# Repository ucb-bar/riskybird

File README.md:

# RiskyBird

RiskyBird is an experimental quadcopter platform for hardware-software-mechanical co-design of tiny autonomous robots.

## Overview

This repository contains multiple iterations of RiskyBird hardware designs:

- **riskybirdv2_sensor/** - Sensor board with IMU, optical flow, and camera interface
- **riskybirdv2_esp/** - ESP32-based flight controller
- **riskybirdv2_k230d/** - K230D-based compute module
- **riskybirdv3_base/** - Latest iteration with integrated base board design
- **ecad/** & **ecad_2025/** - Electronic CAD files and libraries

## Design Goals

- Miniaturized form factor for agile flight
- Modular sensor and compute architecture
- On-board ML inference capability
- Rapid prototyping and iteration

## Hardware

The platform uses KiCad for PCB design and integrates:
- Low-cost sensors (IMU, optical flow, cameras)
- ESP32 for real-time control
- Optional AI accelerator (K230D) for perception
- Custom power distribution and motor control

## Educational Content

See [riskybird-academy/](riskybird-academy/) for tutorial materials covering embedded ML, robotics, and reinforcement learning.

## License

Hardware designs and educational materials are open source for non-commercial use.

Contact: vnikiforov@berkeley.edu

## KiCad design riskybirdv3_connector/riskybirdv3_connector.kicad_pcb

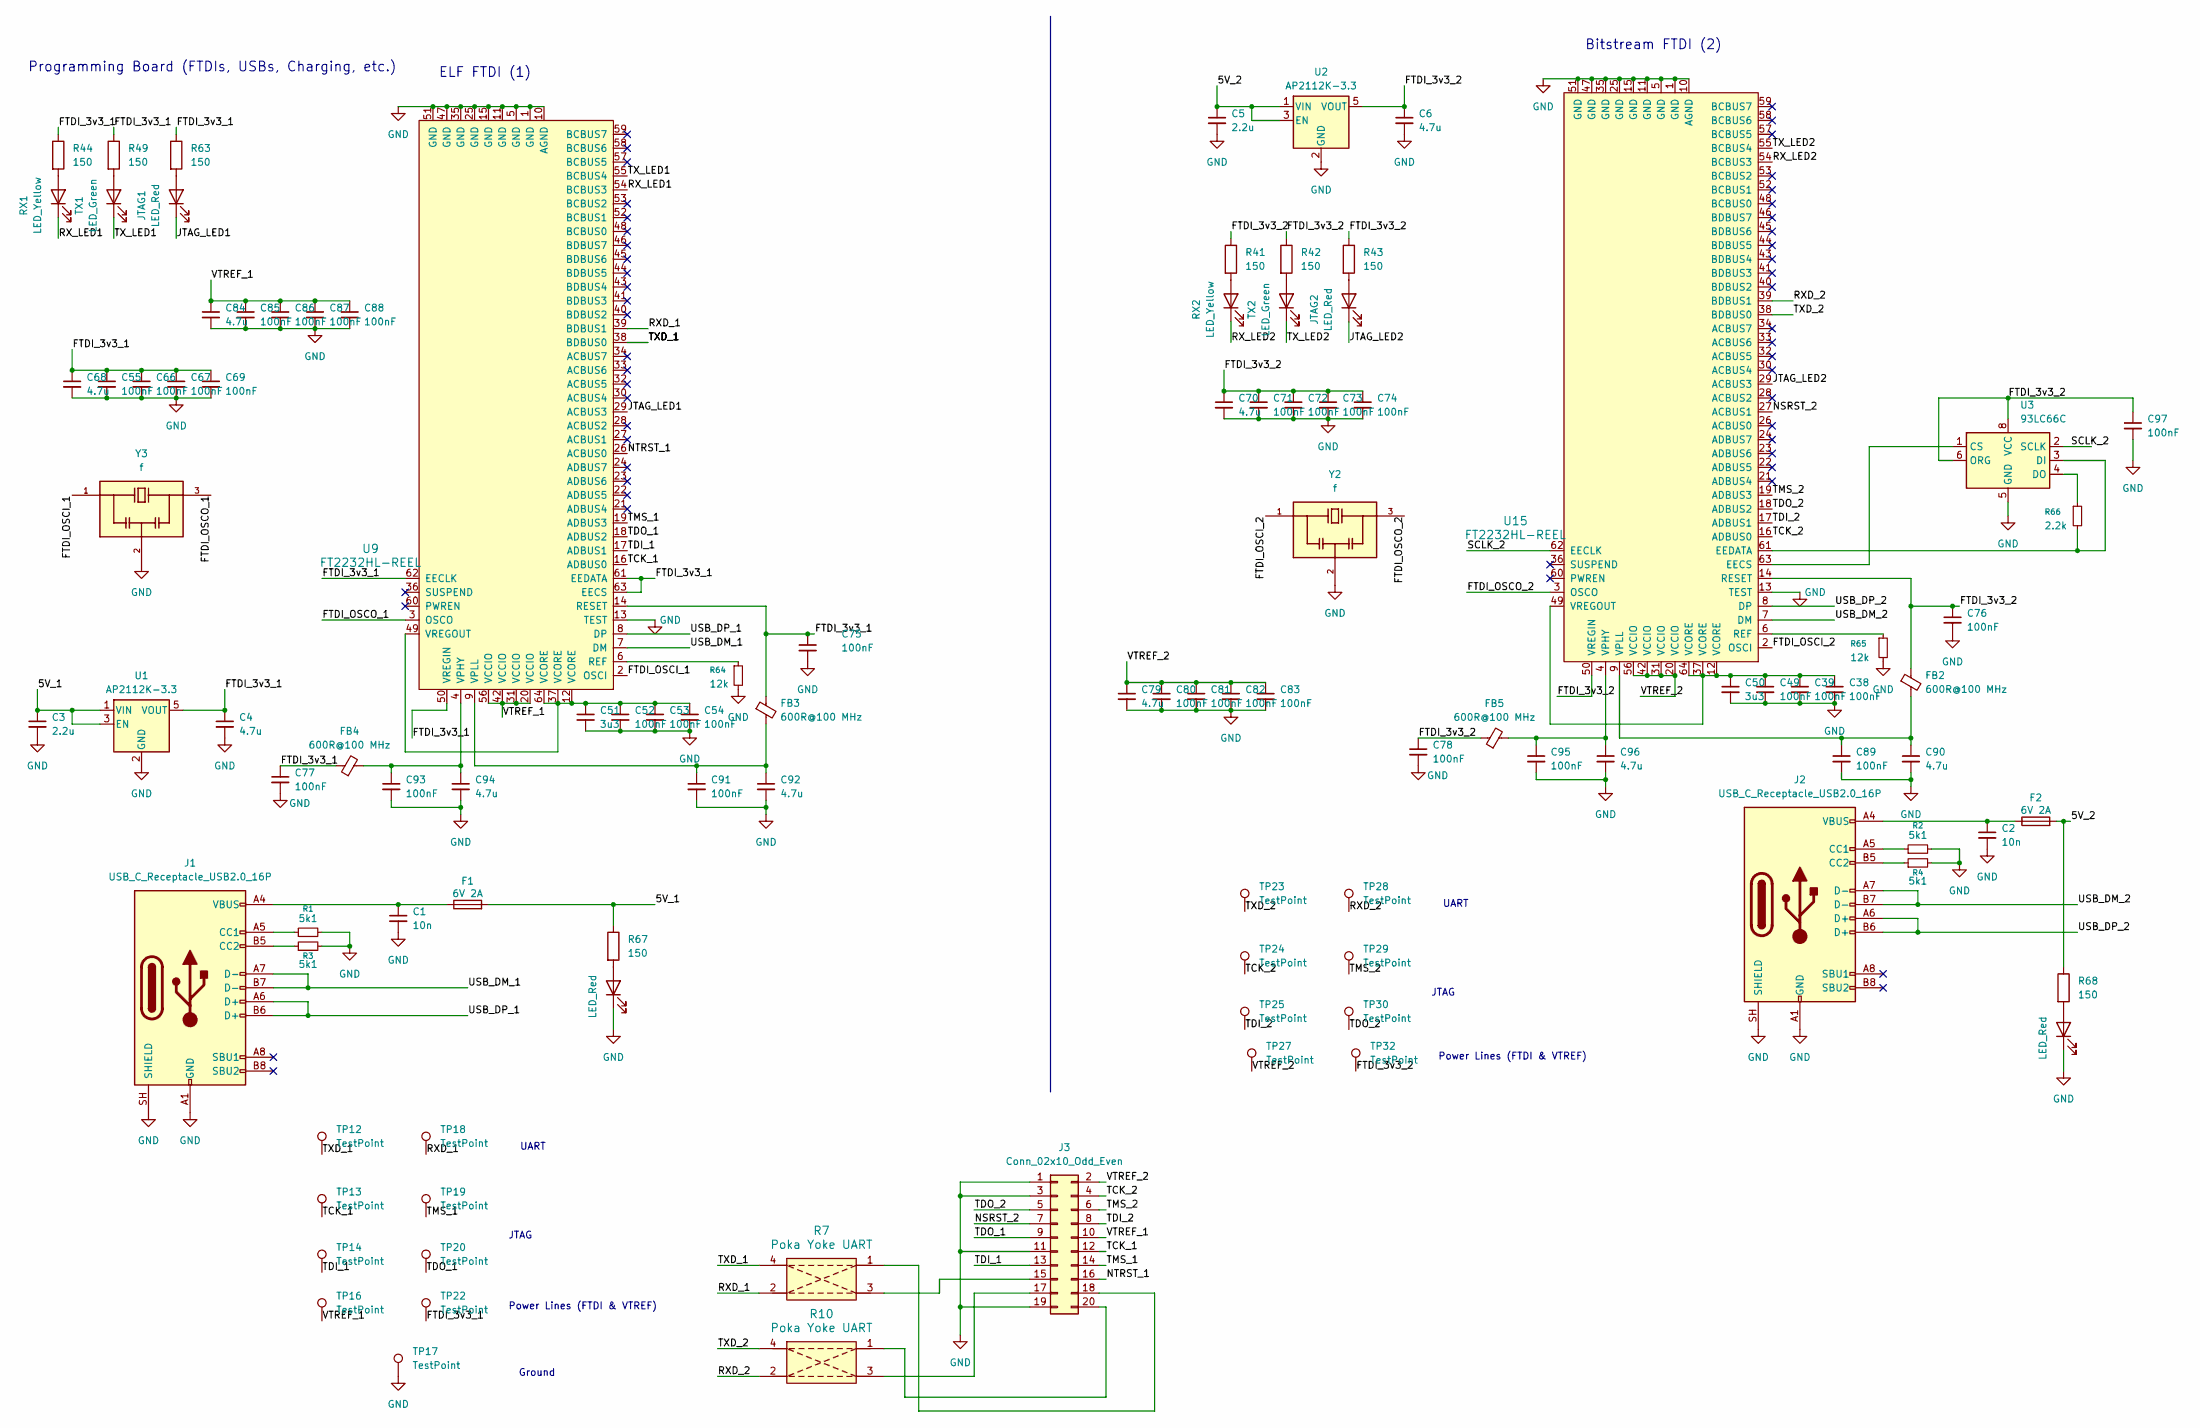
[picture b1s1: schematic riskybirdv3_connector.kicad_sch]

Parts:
C1, C2: 10n; C_0201_0603Metric; MPN 0201B103K250NT; LCSC Part C285010
C3, C5: 2.2u; C_0201_0603Metric; MPN GRM033R61A225ME47D; LCSC Part C319184
C4, C6, C68, C70, C79, C84: 4.7u; C_0201_0603Metric; MPN GRM035R60J475ME15D; LCSC Part C335103
C38, C39, C49, C52, C53, C54, C55, C66, C67, C69, C71, C72, C73, C74, C75, C76, C77, C78, C80, C81, C82, C83, C85, C86, C87, C88, C89, C91, C93, C95, C97: 100nF; C_0201_0603Metric; MPN GRM033R61E104KE14D; LCSC Part C76939
C50, C51: 3u3; C_0201_0603Metric; MPN CL03A305MQ37RNZ; LCSC Part C514591
C90, C92, C94, C96: 4.7u; C_0402_1005Metric; MPN GRM033R61E104KE14D; LCSC Part C76939
F1, F2: 6V 2A; Fuse_1210_3225Metric; MPN BSMD1210-200-6V; LCSC Part C914221
FB2, FB3, FB4, FB5: 600R@100 MHz; L_0603_1608Metric; MPN GZ1608D601TF; LCSC Part C1002
J1, J2: USB_C_Receptacle_USB2.0_16P; USB_C_Receptacle_GCT_USB4105-xx-A_16P_TopMnt_Horizontal; MPN USB4105-GF-A-060; LCSC Part C3025063
J3: Conn_02x10_Odd_Even; CONN-SMD_FTSH-110-01-L-DV-K-TR; MPN FTSH-110-01-L-DV-K-TR; LCSC Part C20728453
JTAG1, JTAG2, JTAG3, JTAG4: LED_Red; LED_0402_1005Metric; MPN NCD0402R1; LCSC Part C130719
R1, R2, R3, R4: 5k1; R_0201_0603Metric; MPN 0201WMF5101TEE; LCSC Part C270344
R7, R10: Poka Yoke UART; poka_yoke_uart_SMD
R41, R42, R43, R44, R49, R63, R67, R68: 150; R_0201_0603Metric; MPN RC0201FR-07150RL; LCSC Part C295773
R64, R65: 12k; R_0201_0603Metric; MPN 0201WMF1202TEE; LCSC Part C270363
R66: 2.2k; R_0201_0603Metric; MPN 0201WMF1202TEE; LCSC Part C270363
RX1, RX2: LED_Yellow; LED_0402_1005Metric; MPN SZYY0402Y; LCSC Part C434450
TP12, TP13, TP14, TP16, TP17, TP18, TP19, TP20, TP22, TP23, TP24, TP25, TP27, TP28, TP29, TP30, TP32: TestPoint; TestPoint_Pad_D1.0mm
TX1, TX2: LED_Green; LED_0402_1005Metric; MPN SZYY0402YG; LCSC Part C434449
U1, U2: AP2112K-3.3; SOT-23-5; MPN AP2112K-3.3TRG1; LCSC Part C23380830
U3: 93LC66C; MSOP-8_3x3mm_P0.65mm; MPN 93LC66C-I/MS; LCSC Part C1350907
U9, U15: FT2232HL-REEL; LQFP-64_10x10mm_P0.5mm; MPN FT2232HL-REEL; LCSC Part C27882
Y2, Y3: f; OSC_CSTNE12M0G550000R0; MPN CSTNE12M0G550000R0; LCSC Part C341520

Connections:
/5V_1: C3.1, F1.2, R67.1, U1.1 (VIN), U1.3 (EN)
/5V_2: C5.1, F2.2, R68.1, U2.1 (VIN), U2.3 (EN)
/FTDI_3v3_1: C4.1, C55.1, C66.1, C67.1, C68.1, C69.1, C75.1, C77.1, FB3.1, FB4.1, R44.1, R49.1, R63.1, TP22.1 (1_1), U1.5 (VOUT), U9.14 (RESET), U9.50 (VREGIN), U9.61 (EEDATA), U9.62 (EECLK), U9.63 (EECS)
/FTDI_3v3_2: C6.1, C70.1, C71.1, C72.1, C73.1, C74.1, C76.1, C78.1, C97.1, FB2.1, FB5.1, R41.1, R42.1, R43.1, TP32.1 (1_1), U2.5 (VOUT), U3.6 (ORG), U3.8 (VCC), U15.14 (RESET), U15.50 (VREGIN)
/FTDI_OSCI_1: U9.2 (OSCI), Y3.1
/FTDI_OSCI_2: U15.2 (OSCI), Y2.1
/FTDI_OSCO_1: U9.3 (OSCO), Y3.3
/FTDI_OSCO_2: U15.3 (OSCO), Y2.3
/JTAG_LED1: JTAG1.1 (K), U9.29 (ACBUS3)
/JTAG_LED2: JTAG2.1 (K), U15.29 (ACBUS3)
/NSRST_2: J3.7, U15.27 (ACBUS1)
/NTRST_1: J3.16, U9.26 (ACBUS0)
/RXD_1: R7.2, TP18.1 (1_1), U9.39 (BDBUS1)
/RXD_2: R10.2, TP28.1 (1_1), U15.39 (BDBUS1)
/RX_LED1: RX1.1 (K), U9.54 (BCBUS3)
/RX_LED2: RX2.1 (K), U15.54 (BCBUS3)
/SCLK_2: U3.2 (SCLK), U15.62 (EECLK)
/TCK_1: J3.12, TP13.1 (1_1), U9.16 (ADBUS0)
/TCK_2: J3.4, TP24.1 (1_1), U15.16 (ADBUS0)
/TDI_1: J3.13, TP14.1 (1_1), U9.17 (ADBUS1)
/TDI_2: J3.8, TP25.1 (1_1), U15.17 (ADBUS1)
/TDO_1: J3.9, TP20.1 (1_1), U9.18 (ADBUS2)
/TDO_2: J3.5, TP30.1 (1_1), U15.18 (ADBUS2)
/TMS_1: J3.14, TP19.1 (1_1), U9.19 (ADBUS3)
/TMS_2: J3.6, TP29.1 (1_1), U15.19 (ADBUS3)
/TXD_1: R7.4, TP12.1 (1_1), U9.38 (BDBUS0)
/TXD_2: R10.4, TP23.1 (1_1), U15.38 (BDBUS0)
/TX_LED1: TX1.1 (K), U9.55 (BCBUS4)
/TX_LED2: TX2.1 (K), U15.55 (BCBUS4)
/USB_DM_1: J1.A7 (D-), J1.B7 (D-), U9.7 (DM)
/USB_DM_2: J2.A7 (D-), J2.B7 (D-), U15.7 (DM)
/USB_DP_1: J1.A6 (D+), J1.B6 (D+), U9.8 (DP)
/USB_DP_2: J2.A6 (D+), J2.B6 (D+), U15.8 (DP)
/VTREF_1: C84.1, C85.1, C86.1, C87.1, C88.1, J3.10, TP16.1 (1_1), U9.20 (VCCIO), U9.31 (VCCIO), U9.42 (VCCIO), U9.56 (VCCIO)
/VTREF_2: C79.1, C80.1, C81.1, C82.1, C83.1, J3.2, TP27.1 (1_1), U15.20 (VCCIO), U15.31 (VCCIO), U15.42 (VCCIO), U15.56 (VCCIO)
GND: C1.2, C2.2, C3.2, C4.2, C5.2, C6.2, C38.2, C39.2, C49.2, C50.2, C51.2, C52.2, C53.2, C54.2, C55.2, C66.2, C67.2, C68.2, C69.2, C70.2, C71.2, C72.2, C73.2, C74.2, C75.2, C76.2, C77.2, C78.2, C79.2, C80.2, C81.2, C82.2, C83.2, C84.2, C85.2, C86.2, C87.2, C88.2, C89.2, C90.2, C91.2, C92.2, C93.2, C94.2, C95.2, C96.2, C97.2, J1.A1 (GND), J1.A12 (GND), J1.B1 (GND), J1.B12 (GND), J1.SH (SHIELD), J2.A1 (GND), J2.A12 (GND), J2.B1 (GND), J2.B12 (GND), J2.SH (SHIELD), J3.1, J3.3, J3.11, J3.19, JTAG3.1 (K), JTAG4.1 (K), R1.2, R2.2, R3.2, R4.2, R64.2, R65.2, TP17.1 (1_1), U1.2 (GND), U2.2 (GND), U3.5 (GND), U9.1 (GND), U9.5 (GND), U9.10 (AGND), U9.11 (GND), U9.13 (TEST), U9.15 (GND), U9.25 (GND), U9.35 (GND), U9.47 (GND), U9.51 (GND), U15.1 (GND), U15.5 (GND), U15.10 (AGND), U15.11 (GND), U15.13 (TEST), U15.15 (GND), U15.25 (GND), U15.35 (GND), U15.47 (GND), U15.51 (GND), Y2.2, Y3.2
unnamed: C1.1, F1.1, J1.A4 (VBUS), J1.A9 (VBUS), J1.B4 (VBUS), J1.B9 (VBUS)
unnamed: C2.1, F2.1, J2.A4 (VBUS), J2.A9 (VBUS), J2.B4 (VBUS), J2.B9 (VBUS)
unnamed: J1.A5 (CC1), R1.1
unnamed: J1.B5 (CC2), R3.1
unnamed: J2.A5 (CC1), R2.1
unnamed: J2.B5 (CC2), R4.1
unnamed: J3.15, R7.3
unnamed: J3.17, R10.3
unnamed: J3.18, R7.1
unnamed: J3.20, R10.1
unnamed: JTAG1.2 (A), R63.2
unnamed: JTAG2.2 (A), R43.2
unnamed: JTAG3.2 (A), R67.2
unnamed: JTAG4.2 (A), R68.2
unnamed: R44.2, RX1.2 (A)
unnamed: R41.2, RX2.2 (A)
unnamed: R49.2, TX1.2 (A)
unnamed: R42.2, TX2.2 (A)
unnamed: R66.1, U3.4 (DO)
unnamed: R64.1, U9.6 (REF)
unnamed: C93.1, C94.1, FB4.2, U9.4 (VPHY)
unnamed: C91.1, C92.1, FB3.2, U9.9 (VPLL)
unnamed: C51.1, C52.1, C53.1, C54.1, U9.12 (VCORE), U9.37 (VCORE), U9.49 (VREGOUT), U9.64 (VCORE)
unnamed: U3.1 (CS), U15.63 (EECS)
unnamed: R66.2, U3.3 (DI), U15.61 (EEDATA)
unnamed: R65.1, U15.6 (REF)
unnamed: C95.1, C96.1, FB5.2, U15.4 (VPHY)
unnamed: C89.1, C90.1, FB2.2, U15.9 (VPLL)
unnamed: C38.1, C39.1, C49.1, C50.1, U15.12 (VCORE), U15.37 (VCORE), U15.49 (VREGOUT), U15.64 (VCORE)

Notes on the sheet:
Programming Board (FTDIs, USBs, Charging, etc.)
JTAG
UART
ELF FTDI (1)
Power Lines (FTDI & VTREF)
Bitstream FTDI (2)
Ground

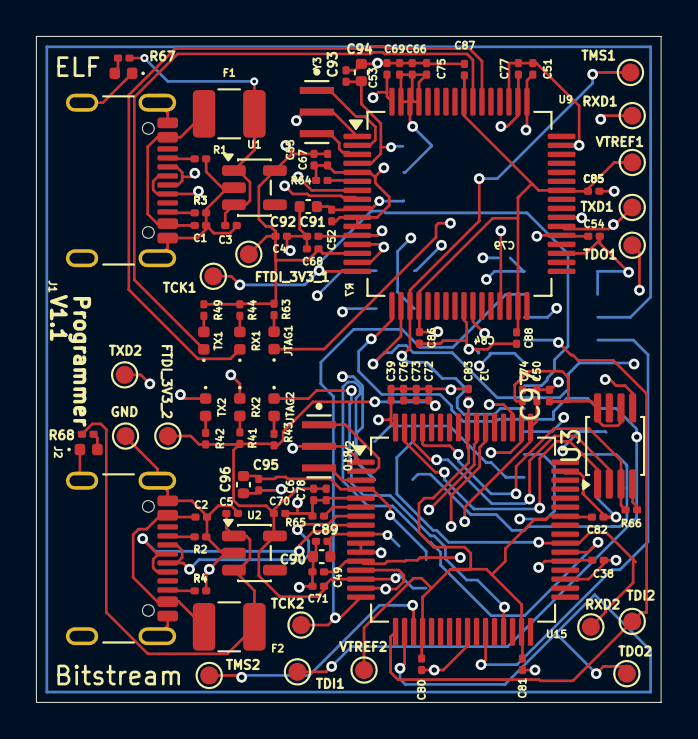
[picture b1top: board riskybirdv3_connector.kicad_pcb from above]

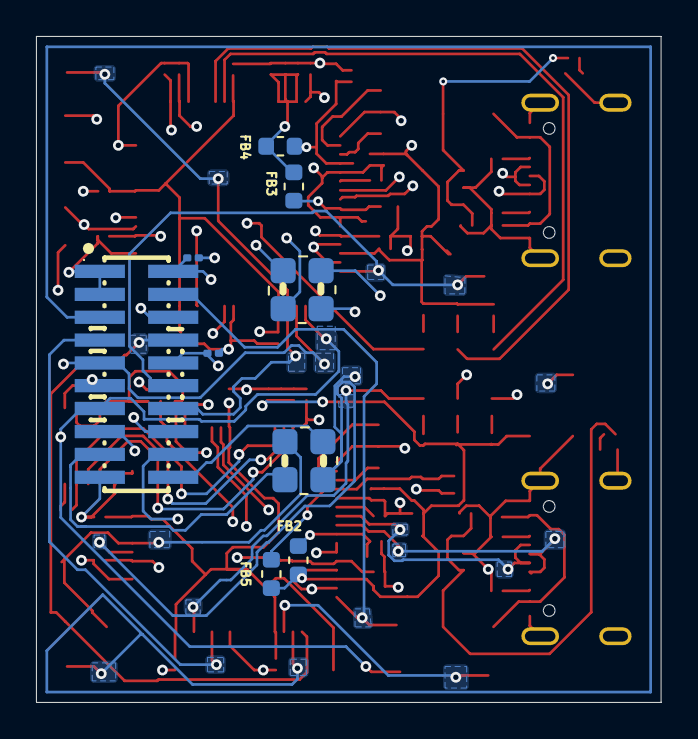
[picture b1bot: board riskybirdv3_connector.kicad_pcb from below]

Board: 4 copper layers, 34.7 x 37.0 mm, 105 parts (9 on the bottom side), 65 nets.
